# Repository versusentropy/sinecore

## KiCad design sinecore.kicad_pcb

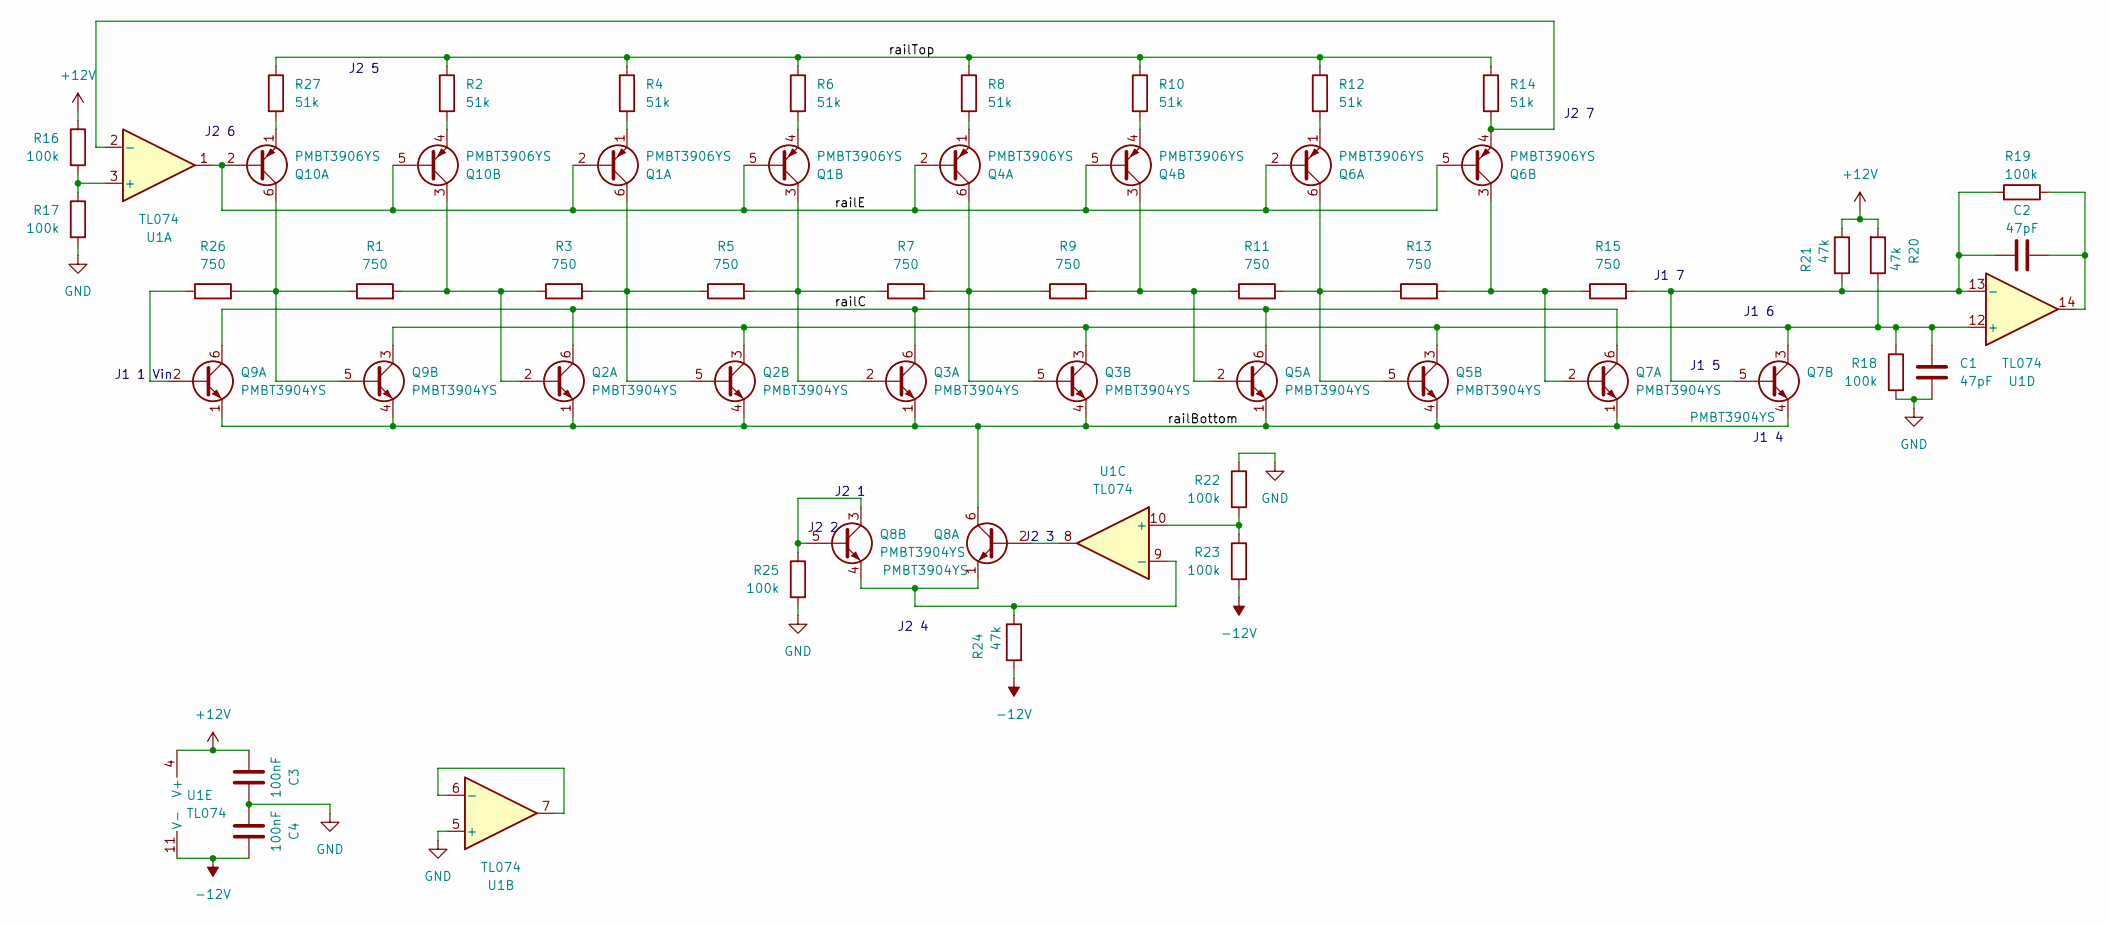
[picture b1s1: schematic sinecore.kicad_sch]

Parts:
C1, C2: 47pF; C_0402_1005Metric
C3, C4: 100nF; C_0402_1005Metric
Q1, Q4, Q6, Q10: PMBT3906YS; SOT-363_SC-70-6
Q2, Q3, Q5, Q7, Q8, Q9: PMBT3904YS; SOT-363_SC-70-6
R1, R3, R5, R7, R9, R11, R13, R15, R26: 750; R_0402_1005Metric
R2, R4, R6, R8, R10, R12, R14, R27: 51k; R_0402_1005Metric
R16, R17, R18, R19, R22, R23, R25: 100k; R_0402_1005Metric
R20, R21, R24: 47k; R_0402_1005Metric
U1: TL074; TSSOP-14_4.4x5mm_P0.65mm

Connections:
+12V: C3.1, R16.1, R20.2, R21.1, U1.4 (V+)
-12V: C4.2, R23.2, R24.2, U1.11 (V-)
/railBottom: Q2.1 (E1), Q2.4 (E2), Q3.1 (E1), Q3.4 (E2), Q5.1 (E1), Q5.4 (E2), Q7.1 (E1), Q7.4 (E2), Q8.6 (C1), Q9.1 (E1), Q9.4 (E2)
/railC: Q2.6 (C1), Q3.6 (C1), Q5.6 (C1), Q7.6 (C1), Q9.6 (C1)
/railE: Q1.2 (B1), Q1.5 (B2), Q4.2 (B1), Q4.5 (B2), Q6.2 (B1), Q6.5 (B2), Q10.2 (B1), Q10.5 (B2), U1.1
/railTop: R2.1, R4.1, R6.1, R8.1, R10.1, R12.1, R14.1, R27.1
GND: C1.2, C3.2, C4.1, R17.2, R18.2, R22.1, R25.2, U1.5 (+)
unnamed: C2.2, R19.1, U1.14
unnamed: Q1.6 (C1), Q2.5 (B2), R3.2, R5.1
unnamed: Q1.1 (E1), R4.2
unnamed: Q1.3 (C2), Q3.2 (B1), R5.2, R7.1
unnamed: Q1.4 (E2), R6.2
unnamed: C1.1, Q2.3 (C2), Q3.3 (C2), Q5.3 (C2), Q7.3 (C2), Q9.3 (C2), R18.1, R20.1, U1.12 (+)
unnamed: Q3.5 (B2), Q4.6 (C1), R7.2, R9.1
unnamed: Q4.1 (E1), R8.2
unnamed: Q4.3 (C2), Q5.2 (B1), R9.2, R11.1
unnamed: Q4.4 (E2), R10.2
unnamed: Q5.5 (B2), Q6.6 (C1), R11.2, R13.1
unnamed: Q6.1 (E1), R12.2
unnamed: Q6.3 (C2), Q7.2 (B1), R13.2, R15.1
unnamed: Q6.4 (E2), R14.2, U1.2 (-)
unnamed: C2.1, Q7.5 (B2), R15.2, R19.2, R21.2, U1.13 (-)
unnamed: Q8.2 (B1), U1.8
unnamed: Q8.1 (E1), Q8.4 (E2), R24.1, U1.9 (-)
unnamed: Q8.3 (C2), Q8.5 (B2), R25.1
unnamed: Q9.2 (B1), R26.1
unnamed: Q9.5 (B2), Q10.6 (C1), R1.1, R26.2
unnamed: Q10.1 (E1), R27.2
unnamed: Q2.2 (B1), Q10.3 (C2), R1.2, R3.1
unnamed: Q10.4 (E2), R2.2
unnamed: R16.2, R17.1, U1.3 (+)
unnamed: U1.6 (-), U1.7
unnamed: R22.2, R23.1, U1.10 (+)

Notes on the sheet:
J2 1
J2 5
J1 4
J2 3
J1 7
J1 1 Vin
J2 6
J1 6
J2 2
J1 5
J2 4
J2 7

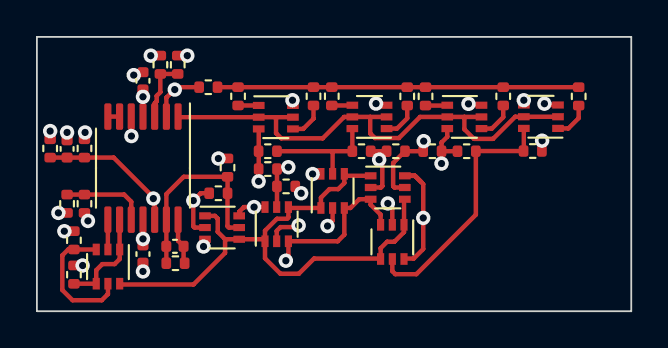
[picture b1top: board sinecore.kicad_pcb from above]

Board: 4 copper layers, 33.0 x 15.2 mm, 42 parts (0 on the bottom side), 33 nets.

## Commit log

2024-08-12 init
2024-08-12 cleanup
